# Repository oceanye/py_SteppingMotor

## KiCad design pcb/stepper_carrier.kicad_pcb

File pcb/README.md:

# ESP32-S3 六路 DM422 + 三路 DRV8871 模块载板

> **历史硬件存档：DM422/DM442 已被 X42S 替换。** 本目录的板图、BOM和生成器
> 不代表当前 X42S 接线方案，不应据此直接打样或接线。本次保留历史原件，不重新生成PCB。

这是一块面向当前 `esp32s3_gear` 固件的 **180 × 210 mm 双层模块载板**。设计目标是把现有成品模块和外部驱动器可靠地接起来，而不是把 ESP32、DRV8871、DM422、TCA9548A、PCF8575 或 RS485 模块拆成芯片级电路。

板上支持：

- 1 块 ESP32-S3-DevKitC-1（2×22P 排母插接）；
- 6 套外置 DM422 的 PUL/DIR 信号端子；
- 2 块闭环 GEAR 用 DRV8871 成品模块及 2 路编码器端子；
- 第 3 块独立 DRV8871 成品模块，用于轨道 D 前进/后退；
- 1 块可选/DNP 的 TCA9548A 成品模块和 6 组 `3V3/GND/SDAx/SCLx` AS5600 接口；
- 1 块可选/DNP 的 PCF8575 成品模块，P0-P5 预留 DIR0-DIR5、P6-P11 预留 ENA0-ENA5；
- 1 组 3.3 V 多功能扩展排针；GPIO42/47 可作共享 I²C SDA/SCL，也可在停用 I²C 后改作 UART/RS485；
- 1 个可选的成品 RS485 收发模块占位及 A/B/GND 端子；
- 全板公共 GND、独立 `3V3` / `5V_USB` / `VM_MOTOR` 电源域。

> **本版本的模块机械尺寸均为 MOCK。禁止按当前占位直接批量打样。拿到实物后先测量模块外形、排针中心距、孔位和引脚顺序，再修改 `generate_pcb.py` 顶部的 `MODULE_GEOMETRY`。**

## 模块接入硬约束

本板只做**完整成品模块的载板**，不把任何模块拆回芯片级电路：

| 对象 | 当前接入方式 | 后续允许的替代方式 |
|---|---|---|
| ESP32-S3 DevKit | 2×22P、2.54 mm 排母插接 | 仅在更换为带邮票孔的完整 ESP32 模组板后制作其专用封装 |
| DRV8871 ×3 | 完整驱动模块通过排针/排母插接，电机端仍使用模块自带端子 | 按真实模块邮票孔制作专用封装 |
| TCA9548A | 完整多路复用模块通过排针/排母插接 | 按真实模块邮票孔制作专用封装 |
| PCF8575 | 完整 GPIO 扩展模块通过排针/排母插接 | 按真实模块邮票孔制作专用封装 |
| RS485 | 完整收发模块通过排针/排母插接 | 按真实模块邮票孔制作专用封装 |
| AS5600 ×6 | 完整传感器模块安装在电机轴端，通过四线端子/线束回到载板 | 若机械结构允许，可把真实模块邮票孔直接焊在轴端小板，不能把传感器芯片直接放到主载板 |
| DM422/DM442 | 完整外置驱动器，通过PUL/DIR端子线束连接 | 不安装到本载板，也不拆解其功率级 |

排针方案适合当前尺寸未定、需要更换和调试的阶段。邮票孔只适用于**模块本身已经提供邮票孔边缘焊盘**的情况；必须拿到实物或正式机械图后，按边缘焊盘节距、长度、板边偏移、模块外形和底部禁布区制作专用 footprint。不存在可安全通用的“任意模块邮票孔封装”。

当前 KiCad 文件采用排针/通孔模块插座作为 MOCK 基线。后续确认某个模块使用邮票孔时，只替换该模块 footprint，保持网络名、固件引脚和其他模块不变。

## 文件

| 文件 | 用途 |
|---|---|
| `generate_pcb.py` | 设计单一数据源：网络、引脚、模块占位、布线、丝印 |
| `stepper_carrier.kicad_pcb` | 生成的 KiCad 8 PCB |
| `stepper_carrier.kicad_pro` | KiCad 工程 |
| `preview_pcb.py` / `preview.svg` | 不依赖 KiCad 的布局预览 |

本项目暂时没有原理图，网络关系由生成脚本直接写入 PCB。不要在 KiCad 中执行“从原理图更新 PCB”。

## 集中机械假设

所有可替换参数都集中在 `generate_pcb.py::MODULE_GEOMETRY`：

| 模块 | 当前 MOCK 假设 | 下次必须实测 |
|---|---|---|
| ESP32-S3-DevKitC-1 | 官方板框 25.40 × 62.74 mm，2×22P，排距 22.86 mm，针距 2.54 mm | 开发板版本、排距、天线端与 USB 端方向 |
| DRV8871 ×3 | 当前仍按 24 × 20 mm；Adafruit 3190 的 24.4 × 20.4 mm 仅作尺寸量级参考 | 用户现有模块外形、4P 顺序、排针相对板边位置、孔距、VM 额定输入 |
| RS485 模块 | 45 × 20 mm，逻辑侧 2.54 mm，A/B 侧相距 40 mm | 具体成品模块型号、排针布局、是否 3.3 V 逻辑兼容 |
| TCA9548A 模块 | 参考 Soldered 54 × 38 mm，载板 MOCK 包络取 56 × 40 mm | 采购型号长宽、主机针序、SDx/SCx 排列、地址焊盘和板载上拉 |
| PCF8575 模块 | 参考 Adafruit 5611：40.8 × 17.7 mm，载板 MOCK 包络取 43 × 20 mm | 采购模块长宽、主机/P0-P15 针序、地址跳线和板载上拉电压 |
| AS5600 模块 ×6 | 参考 Seeed Grove 101020692：40 × 20 mm；建议轴端预留 42 × 22 mm 包络 | `VCC/GND/SDA/SCL` 针序、3.3V 兼容、孔位、传感器中心和磁铁轴向 |
| Pico/RP2040（未来） | 官方 Raspberry Pi Pico 51 × 21 × 1 mm、2.54 mm 邮票孔/通孔 | 是否实际增加协处理器、USB 端净空、通信和供电方式 |
| KF301 类端子 | 5.08 mm 针距，1.3 mm 钻孔 | 实际品牌的针宽、塑壳尺寸和进线方向 |

具体在线资料、选择理由和可信度见 `MOCK_MODULE_REFERENCES.md`。这些尺寸用于布局空间和采购前评审，除 ESP32-S3 DevKitC-1 与 Raspberry Pi Pico 的官方机械图外，仍不能替代实际采购模块的尺寸与针序复核。

更换实物模块时优先只替换相应模块 footprint，保持逻辑网络名不变。ESP32-S3 引脚依据乐鑫官方 [ESP32-S3-DevKitC-1 v1.1 Header Block](https://docs.espressif.com/projects/esp-dev-kits/en/latest/esp32s3/esp32-s3-devkitc-1/user_guide_v1.1.html#header-block)。

## 固件引脚映射

以下内容与 `esp32_stepper/src/config.h` 的 `DRIVE_MODE_GEAR` 当前定义一致：

| 功能 | GPIO |
|---|---|
| DM422 #0 PUL / DIR | 5 / 6 |
| DM422 #1 PUL / DIR | 7 / 15 |
| DM422 #2 PUL / DIR | 1 / 2 |
| DM422 #3 PUL / DIR | 4 / 8 |
| DM422 #4 PUL / DIR | 9 / 10 |
| DM422 #5 PUL / DIR | 38 / 39 |
| GEAR 0 DRV 实体 IN1 / IN2 | 11 / 16 |
| GEAR 0 编码器实体 A(C1) / B(C2) | 18 / 21 |
| GEAR 1 DRV 实体 IN1 / IN2 | 12 / 17 |
| GEAR 1 编码器实体 A(C1) / B(C2) | 13 / 14 |
| 轨道 D DRV IN1 / IN2 | 40 / 41 |
| 可选编码器诊断 I²C SDA / SCL | 42 / 47 |
| 预留 RS485 DE | 48 |

`config.h` 中 GEAR 的 IN1/IN2 和 ENCA/ENCB 是为了 PID 正方向而交换后的**逻辑名**；上表和 PCB 丝印使用模块、编码器的**实体脚名**。不要把逻辑名直接当作模块脚名。GPIO48 在部分 DevKit 版本连接板载 RGB LED，因此 AUX/RS485 正式启用前必须确认实际开发板版本。

当前编码器尚未安装，六路 DM422/DM442 必须继续使用 ESP32 原生 PUL/DIR 开环链路。
TCA9548A、六块 AS5600 和 PCF8575 均为可选后装/DNP 预留，不得成为当前开环运行的
前置条件。TCA9548A 与 PCF8575 可以在同一 GPIO42/47 I²C 总线上并存；I²C 与 AUX
UART/RS485 互斥，切换用途前必须同步修改固件配置。

## 接口定义

### 六组 DM422 信号

`J_DM0_SIG` 到 `J_DM5_SIG` 均按以下顺序：

| Pin | 信号 | 接 DM422 |
|---|---|---|
| 1 | 对应 GPIO PUL | PUL+ |
| 2 | GND | PUL− |
| 3 | 对应 GPIO DIR | DIR+ |
| 4 | GND | DIR− |

DM422 的 24 V 电机电源 **不经过本载板**。六套 DM422 应使用额定电流足够、带保险的成品 24 V 分配模块或端子排独立布线；24 V 负极与本板 GND 在系统内共地。

**ENA+/ENA- 不经本载板**（`J_DMx_SIG` 只引出 PUL/DIR 4P 信号，每轴只需 PUL+ 和 DIR+ 两根信号线到 ESP32）。DM422/DM442 的 ENA 保持**悬空即默认使能**驱动；如未来要软件控制使能（如急停时失能输出），须经 PCF8575 等扩展器并加成品开集电极/ULN 缓冲模块（当前固件未实现，且 PUL 永远留在 ESP32 原生 GPIO，I²C 扩展器做不了脉冲）。

### DRV8871 成品模块

`U_DRV0`、`U_DRV1`、`U_DRVD` 当前假设模块逻辑排针为：

| Pin | 信号 |
|---|---|
| 1 | VM_MOTOR |
| 2 | GND |
| 3 | IN2 |
| 4 | IN1 |

电机线接 DRV8871 模块自带的 Motor+/Motor− 螺钉端子，不绕回载板。三个模块共用 `J_VM_IN` 的独立低压电机电源。

`J_VM_IN` 只允许接符合 N20 和轨道 D 电机额定电压的低压电源。**不要把 DM422 的 24 V 接到 `J_VM_IN`，也不要把 24 V 直接接到 N20/DRV8871。**

### 编码器

`J_ENC0`、`J_ENC1`：`3V3 / GND / A / B`。若实物编码器输出不是 3.3 V 兼容电平，须使用成品电平转换模块，不要直接接 ESP32。

### UART / I²C / RS485 扩展

`J_AUX_UART`：`5V_USB / 3V3 / GND / TX或SDA(GPIO42) / RX或SCL(GPIO47) / DE(GPIO48)`。

- Pico/RP2040 的 UART 逻辑必须是 3.3 V；
- I²C 模式下 GPIO42/47 分别作为 SDA/SCL，可同时接 TCA9548A 与 PCF8575；
- I²C 只建议承担 DIR、ENA、限位等低速信号，不用于实时生成 DM422 的 PUL；
- `5V_USB` 只来自 DevKit USB/5V 引脚，不与 `VM_MOTOR` 相连；
- 连接外部 Pico 时只选一种供电路径，避免两个 USB 电源互相回灌；
- 可选 `U_RS485` 使用成品 3.3 V RS485 模块，`/RE` 与 `DE` 共用 GPIO48；
- TTL UART、I²C 与 RS485 模块共用 GPIO42/47；I²C 模式与 UART/RS485 模式互斥；
- RS485 外部端子 `J_RS485` 为 `A / B / GND`。

### 可选六路 AS5600 诊断

启用后的诊断拓扑为 GPIO42(SDA) / GPIO47(SCL) → TCA9548A `0x70` → 通道 0–5 →
各一路 AS5600 `0x36`。固件只读取状态，不把数据接入 DM442 的 PUL/DIR 控制：

- `ENC,<axis>,S` 读取轴 0–5 的单行诊断快照；
- AS5600 是单圈绝对编码器；固件的多圈角仅是在本次运行期间按跨零点变化累计；
- 展开算法要求相邻成功采样之间的运动小于半圈；掉线或转速过高时多圈累计可能失真；
- 断电、复位、I²C 长时间掉线后，多圈圈数不可恢复，机械系统必须重新回零；
- 电机附近长线 I²C 抗干扰能力有限，应缩短线长、正确共地和配置上拉，必要时使用
  差分 I²C 延长器；不能把该诊断读数当作安全限位；
- PCF8575 地址 `0x20` 仅在固件中预留，当前 PUL/DIR（包括 DIR）均不经过 PCF8575。

`U_I2CMUX` 是 TCA9548A 成品模块 MOCK 插座；`J_AS0`～`J_AS5` 均为
`3V3 / GND / SDAx / SCLx`。所有 AS5600 必须使用 3.3V 兼容模块。I²C 线应尽量短、
远离电机电源和 PUL 线，核对整条总线的上拉总值；长线应改用成品差分 I²C 延长模块。

### 可选 PCF8575 DIR/ENA 预留

`U_IOEXP` 是 PCF8575 成品模块 MOCK 插座，与 TCA9548A 共用 3.3V I²C：

| 端口 | 规划用途 | 引出接口 |
|---|---|---|
| P0-P5 | DIR0-DIR5 未来逻辑命令 | J_PCF_DIR |
| P6-P11 | ENA0-ENA5 未来逻辑命令 | J_PCF_ENA |
| P12-P15 / INT | 预留 | J_PCF_RSVD |

PCF8575 是准双向端口，源/灌电流和上电状态不能按推挽 GPIO 假定。PCB **没有**把任何
PCF 输出硬连到 DM 输入，原生 PUL/DIR 保持默认直连。未来启用时必须先实测 DM 光耦
电压、电流及共阴/共阳接法，再使用经确认的成品开集电极、ULN 类或隔离驱动模块；
PCF raw header 只接缓冲模块逻辑输入。六路 PUL 始终由 ESP32 原生 GPIO 产生。

TCA、PCF 和 AS 模块只能使用 3.3V I²C 上拉。禁止把模块上的 5V SDA/SCL 上拉直接送入
ESP32；若实物模块只能 5V 工作，必须增加成品双向电平转换模块。

## 电源与接地边界

| 电源域 | 来源 | 仅用于 | 明确禁止 |
|---|---|---|---|
| DM422 24 V | 板外保险分配模块 | 六套外置 DM422 | 进入本载板、DRV8871、N20、编码器 |
| VM_MOTOR | `J_VM_IN` 独立低压源 | 三块 DRV8871 和相应电机 | 与 24 V 在板上短接 |
| 5V_USB | DevKit 5V 脚 | AUX 扩展可选供电 | 驱动电机 |
| 3V3 | DevKit 3V3 脚 | 编码器、TCA/PCF、AUX/RS485 逻辑 | 驱动电机、接入 5V I²C 上拉 |
| GND | 全板 F.Cu 地平面 | 所有控制信号参考 | 与外部 DM422 负极悬空 |

## 模块化 BOM

| 物料 | 数量 | 备注 |
|---|---:|---|
| ESP32-S3-DevKitC-1 | 1 | 2×22P，实测版本 |
| 1×22P 2.54 mm 排母 | 2 | DevKit 插座 |
| DM422 成品驱动器 | 6 | 板外安装和 24 V 供电 |
| DRV8871 成品模块 | 3 | GEAR 0、GEAR 1、轨道 D |
| 1×4P 2.54 mm 排母 | 3 | 以实物模块排针为准 |
| KF301 类 5.08 mm 4P | 14 | 6×DM 信号 + 2×GEAR 编码器 + 6×AS5600 |
| KF301 类 5.08 mm 2P | 1 | VM_MOTOR 输入 |
| KF301 类 5.08 mm 3P | 1 | RS485 A/B/GND |
| 1×6P 2.54 mm 排针/排母 | 1 | AUX UART |
| 3.3 V RS485 成品模块 | 0 或 1 | 可选，实测封装 |
| TCA9548A 成品模块 | 0 或 1 | 可选/DNP，解决 6×AS5600 固定 0x36 地址 |
| AS5600 成品模块 | 0～6 | 可选/DNP，分阶段后装 |
| PCF8575 成品模块 | 0 或 1 | 可选/DNP，只作 DIR/ENA 逻辑预留 |
| 成品开集电极/ULN/隔离驱动模块 | 0 或 1 组 | PCF 后装时才选型，当前不装 |
| 2.54 mm PCF raw logic 排针 | 3 组 | DIR/ENA/预留，当前 DNP |
| M3 安装柱 | 4 | 载板四角固定；实物装配若需中部支撑再加孔 |
| 带保险的 24 V 成品分配模块 | 1 | 板外，为 6 套 DM422 供电 |

## 更新与打样前检查

1. 修改 `MODULE_GEOMETRY` 和模块 pin helper，使其与实物完全一致。
2. 从项目根目录运行 `python pcb/generate_pcb.py`，再运行 `python pcb/preview_pcb.py`。
3. 用 KiCad 8/9 打开 `stepper_carrier.kicad_pro`，重新填充铜区并运行 DRC。
4. 核对全部连接器进线方向、丝印可读性、模块 USB 口和天线净空。
5. 用万用表检查 `VM_MOTOR` 与任何 24 V 线束无连接，3V3/5V/VM/GND 无短路。
6. 只有完成实物尺寸核验、DRC 和电源检查后才生成 Gerber。

## HANDOFF：后装前必须确认

- **真实尺寸**：TCA9548A、PCF8575、AS5600、DRV8871 的长宽、排针坐标、孔位和高度。
- **真实针序**：TCA 主机/通道脚、PCF 主机/P0-P15、AS5600 四线接口、DRV8871 逻辑脚。
- **真实电平**：两块 I²C 模块在 3.3V 下可工作，SDA/SCL 板载上拉确实到 3.3V。
- **地址/跳线**：TCA 与 PCF 的 A0-A2 实际默认状态，不能只依据网店描述。
- **DM 输入级**：每种 DM422/DM442 的光耦电压、电流、共阴/共阳方式及所需成品缓冲模块。
- **当前 DNP**：U_I2CMUX、U_IOEXP、J_AS0-J_AS5、PCF raw headers 均先不装，原生六轴开环不变。
- **分阶段落地**：先验证 TCA+1 个 AS5600，再扩到 6 个；PCF 先空载验证，再接成品驱动模块，最后才通过可恢复线束切换 DIR/ENA。

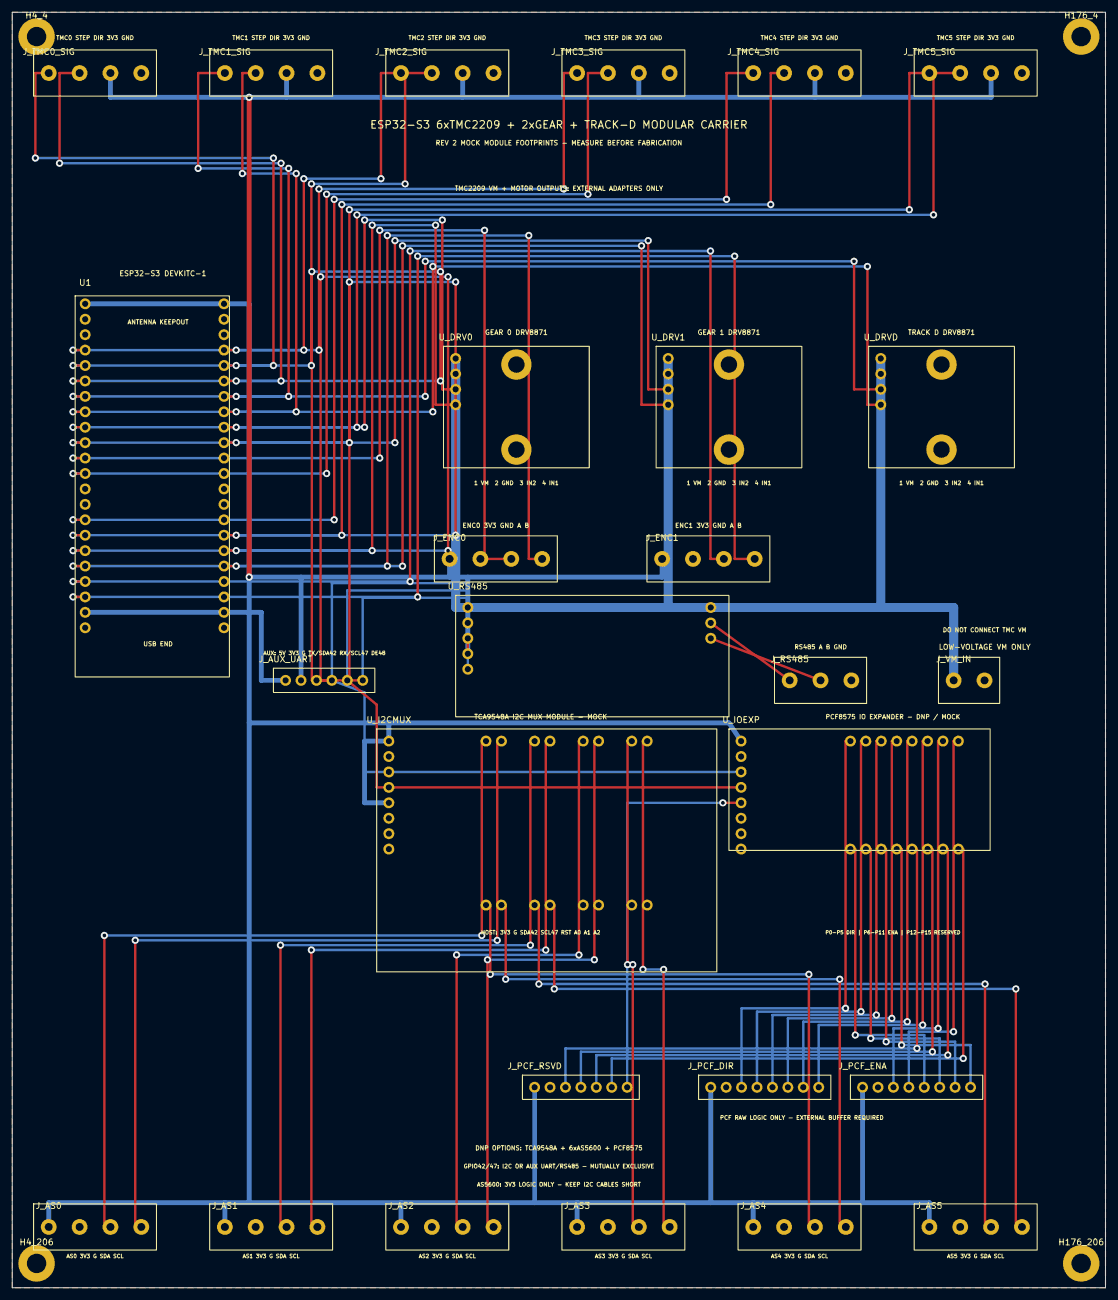
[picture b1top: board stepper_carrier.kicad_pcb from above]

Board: 2 copper layers, 180.0 x 210.0 mm, 31 parts (0 on the bottom side), 60 nets.

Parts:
H4_4, H4_206, H176_4, H176_206: M3; MountingHole_M3
J_AS0: AS5600 #0 CH0; TerminalBlock_1x4_P5.08
J_AS1: AS5600 #1 CH1; TerminalBlock_1x4_P5.08
J_AS2: AS5600 #2 CH2; TerminalBlock_1x4_P5.08
J_AS3: AS5600 #3 CH3; TerminalBlock_1x4_P5.08
J_AS4: AS5600 #4 CH4; TerminalBlock_1x4_P5.08
J_AS5: AS5600 #5 CH5; TerminalBlock_1x4_P5.08
J_AUX_UART: Pico/RP2040 AUX UART or I2C; PinHeader_1x06_P2.54
J_ENC0: GEAR 0 ENCODER; TerminalBlock_1x4_P5.08
J_ENC1: GEAR 1 ENCODER; TerminalBlock_1x4_P5.08
J_PCF_DIR: PCF LOGIC ONLY: 3V3 G P0..P5; PinHeader_1x08_P2.54
J_PCF_ENA: PCF LOGIC ONLY: 3V3 G P6..P11; PinHeader_1x08_P2.54
J_PCF_RSVD: PCF RESERVED: 3V3 G P12..P15 INT; PinHeader_1x07_P2.54
J_RS485: RS485 BUS; TerminalBlock_1x3_P5.08
J_TMC0_SIG: TMC2209 #0 STEP/DIR/VIO/GND; TerminalBlock_1x4_P5.08
J_TMC1_SIG: TMC2209 #1 STEP/DIR/VIO/GND; TerminalBlock_1x4_P5.08
J_TMC2_SIG: TMC2209 #2 STEP/DIR/VIO/GND; TerminalBlock_1x4_P5.08
J_TMC3_SIG: TMC2209 #3 STEP/DIR/VIO/GND; TerminalBlock_1x4_P5.08
J_TMC4_SIG: TMC2209 #4 STEP/DIR/VIO/GND; TerminalBlock_1x4_P5.08
J_TMC5_SIG: TMC2209 #5 STEP/DIR/VIO/GND; TerminalBlock_1x4_P5.08
J_VM_IN: N20/TRACK LOW-VOLTAGE VM INPUT; TerminalBlock_1x2_P5.08
U1: ESP32-S3 DevKitC-1 module (MOCK VERIFY); ModuleSocket_ESP32-S3-DevKitC-1_2x22
U_DRV0: GEAR 0 DRV8871 module (MOCK VERIFY PIN ORDER); ModuleSocket_DRV8871_1x4
U_DRV1: GEAR 1 DRV8871 module (MOCK VERIFY PIN ORDER); ModuleSocket_DRV8871_1x4
U_DRVD: TRACK D DRV8871 module (MOCK VERIFY PIN ORDER); ModuleSocket_DRV8871_1x4
U_I2CMUX: TCA9548A READY-MADE MODULE (MOCK VERIFY ALL PINS); ModuleSocket_TCA9548A_8CH_MOCK
U_IOEXP: PCF8575 READY-MADE MODULE (DNP MOCK VERIFY ALL PI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; ModuleSocket_PCF8575_16IO_MOCK
U_RS485: 3V3 RS485 TRANSCEIVER MODULE (MOCK); ModuleSocket_RS485_Generic

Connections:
3V3: J_AS0.1, J_AS1.1, J_AS2.1, J_AS3.1, J_AS4.1, J_AS5.1, J_AUX_UART.2, J_ENC0.1, J_ENC1.1, J_PCF_DIR.1, J_PCF_ENA.1, J_PCF_RSVD.1, J_TMC0_SIG.3, J_TMC1_SIG.3, J_TMC2_SIG.3, J_TMC3_SIG.3, J_TMC4_SIG.3, J_TMC5_SIG.3, U1.L1, U1.L2, U_I2CMUX.3V3, U_I2CMUX.RST, U_IOEXP.3V3, U_RS485.VCC
5V_USB: J_AUX_UART.1, U1.L21
AS0_SCL: J_AS0.4, U_I2CMUX.SC0
AS0_SDA: J_AS0.3, U_I2CMUX.SD0
AS1_SCL: J_AS1.4, U_I2CMUX.SC1
AS1_SDA: J_AS1.3, U_I2CMUX.SD1
AS2_SCL: J_AS2.4, U_I2CMUX.SC2
AS2_SDA: J_AS2.3, U_I2CMUX.SD2
AS3_SCL: J_AS3.4, U_I2CMUX.SC3
AS3_SDA: J_AS3.3, U_I2CMUX.SD3
AS4_SCL: J_AS4.4, U_I2CMUX.SC4
AS4_SDA: J_AS4.3, U_I2CMUX.SD4
AS5_SCL: J_AS5.4, U_I2CMUX.SC5
AS5_SDA: J_AS5.3, U_I2CMUX.SD5
GND: J_AS0.2, J_AS1.2, J_AS2.2, J_AS3.2, J_AS4.2, J_AS5.2, J_AUX_UART.3, J_ENC0.2, J_ENC1.2, J_PCF_DIR.2, J_PCF_ENA.2, J_PCF_RSVD.2, J_RS485.3, J_TMC0_SIG.4, J_TMC1_SIG.4, J_TMC2_SIG.4, J_TMC3_SIG.4, J_TMC4_SIG.4, J_TMC5_SIG.4, J_VM_IN.2, U1.L22, U1.R1, U1.R21, U1.R22, U_DRV0.2, U_DRV1.2, U_DRVD.2, U_I2CMUX.A0, U_I2CMUX.A1, U_I2CMUX.A2, U_I2CMUX.GND, U_IOEXP.A0, U_IOEXP.A1, U_IOEXP.A2, U_IOEXP.GND, U_RS485.GND
GPIO1: J_TMC2_SIG.1, U1.R4
GPIO2: J_TMC2_SIG.2, U1.R5
GPIO4: J_TMC3_SIG.1, U1.L4
GPIO5: J_TMC0_SIG.1, U1.L5
GPIO6: J_TMC0_SIG.2, U1.L6
GPIO7: J_TMC1_SIG.1, U1.L7
GPIO8: J_TMC3_SIG.2, U1.L12
GPIO9: J_TMC4_SIG.1, U1.L15
GPIO10: J_TMC4_SIG.2, U1.L16
GPIO11: U1.L17, U_DRV0.4
GPIO12: U1.L18, U_DRV1.4
GPIO13: J_ENC1.3, U1.L19
GPIO14: J_ENC1.4, U1.L20
GPIO15: J_TMC1_SIG.2, U1.L8
GPIO16: U1.L9, U_DRV0.3
GPIO17: U1.L10, U_DRV1.3
GPIO18: J_ENC0.3, U1.L11
GPIO21: J_ENC0.4, U1.R18
GPIO38: J_TMC5_SIG.1, U1.R10
GPIO39: J_TMC5_SIG.2, U1.R9
GPIO40: U1.R8, U_DRVD.4
GPIO41: U1.R7, U_DRVD.3
GPIO42: J_AUX_UART.4, U1.R6, U_I2CMUX.SDA, U_IOEXP.SDA, U_RS485.DI
GPIO47: J_AUX_UART.5, U1.R17, U_I2CMUX.SCL, U_IOEXP.SCL, U_RS485.RO
GPIO48: J_AUX_UART.6, U1.R16, U_RS485.DE, U_RS485.RE
PCF_INT: J_PCF_RSVD.7, U_IOEXP.INT
PCF_P0: J_PCF_DIR.3, U_IOEXP.P0
PCF_P1: J_PCF_DIR.4, U_IOEXP.P1
PCF_P2: J_PCF_DIR.5, U_IOEXP.P2
PCF_P3: J_PCF_DIR.6, U_IOEXP.P3
PCF_P4: J_PCF_DIR.7, U_IOEXP.P4
PCF_P5: J_PCF_DIR.8, U_IOEXP.P5
PCF_P6: J_PCF_ENA.3, U_IOEXP.P6
PCF_P7: J_PCF_ENA.4, U_IOEXP.P7
PCF_P8: J_PCF_ENA.5, U_IOEXP.P8
PCF_P9: J_PCF_ENA.6, U_IOEXP.P9
PCF_P10: J_PCF_ENA.7, U_IOEXP.P10
PCF_P11: J_PCF_ENA.8, U_IOEXP.P11
PCF_P12: J_PCF_RSVD.3, U_IOEXP.P12
PCF_P13: J_PCF_RSVD.4, U_IOEXP.P13
PCF_P14: J_PCF_RSVD.5, U_IOEXP.P14
PCF_P15: J_PCF_RSVD.6, U_IOEXP.P15
RS485_A: J_RS485.1, U_RS485.A
RS485_B: J_RS485.2, U_RS485.B
VM_MOTOR: J_VM_IN.1, U_DRV0.1, U_DRV1.1, U_DRVD.1

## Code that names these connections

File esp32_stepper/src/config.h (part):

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#define PIN_GEAR_ENCB_0   18   // ← 物理 C1 当作 B

// ── 减速电机 axis 1（占位，未接硬件；将来装 R 侧 N20 时用） ──
// 载板实体接线为 IN1=GPIO12、IN2=GPIO17、C1/A=GPIO13、C2/B=GPIO14；
// 和 axis 0 一样，这里的逻辑 IN1/IN2、ENCA/ENCB 为统一 PID 正方向而交换。
#define PIN_GEAR_IN1_1    17   // → 实体 IN2
#define PIN_GEAR_IN2_1    12
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#define TRACK_SAFETY_TICK_MS      10

// ── 可选六路步进轴绝对编码器诊断总线（不参与步进控制）──
// GPIO42/47 与载板 AUX UART/RS485 共用，使用本功能时不得同时安装/启用 UART、
// RS485 或其他占用这两个 GPIO 的模块。长线 I2C 易受电机噪声干扰，应使用短线、
// 合理上拉、共地，必要时降低时钟或采用差分 I2C 延长器。
#define STEPPER_ENCODER_DIAGNOSTICS_ENABLED  0  // 编码器尚未安装；安装后显式改为 1
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
// Optional RS485 master for six Raspberry Pi Pico (RP2040) stepper nodes.
// Local axes remain 0..5; nodes 1..6 add global axes 6..29 (four per node).
// GPIO42/47 are shared with the optional diagnostic I2C bus above, so the two
// features are intentionally compile-time exclusive.
#ifndef REMOTE_STEPPER_ENABLED
  #define REMOTE_STEPPER_ENABLED              0
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#define REMOTE_STEPPER_RESPONSE_TIMEOUT_MS      35
#define REMOTE_STEPPER_POLL_INTERVAL_MS          8
#if REMOTE_STEPPER_ENABLED && STEPPER_ENCODER_DIAGNOSTICS_ENABLED
  #error "RS485 remote steppers and GPIO42/47 diagnostic I2C cannot be enabled together"
#endif

// ── 可选 X42S TTL-UART 四轴闭环执行层（feature/x42s-uart-actuator-binding）──
// 与 RS485 remote / 编码器诊断 I2C 共用 GPIO42/47，编译期互斥。
// 功能码/数据布局/状态字已按手册 V1.0.5 核对（2026-09-29，见
// x42s_protocol.h 头注）。步态由 PC 检查在线、使能、遥测及现场基准。
#ifndef X42S_UART_ENABLED
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// FD 梯形位置模式的加/减速度（RPM/S，X 固件单位）。保守起步值，台架标定。
#define X42S_TRAP_ACC_RPM_PS         500
#if X42S_UART_ENABLED && REMOTE_STEPPER_ENABLED
  #error "X42S UART and RS485 remote steppers share GPIO42/47 — pick one"
#endif
#if X42S_UART_ENABLED && STEPPER_ENCODER_DIAGNOSTICS_ENABLED
  #error "X42S UART and GPIO42/47 diagnostic I2C cannot be enabled together"
#endif

// ── 可选硬件急停输入（常闭 NC 接点：GPIO35 ↔ GND + 内部上拉）──
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
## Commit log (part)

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2026-04-22 docs: mark D1 broadcast + D3 PID persistence as done; D4 deferred to post-HW
